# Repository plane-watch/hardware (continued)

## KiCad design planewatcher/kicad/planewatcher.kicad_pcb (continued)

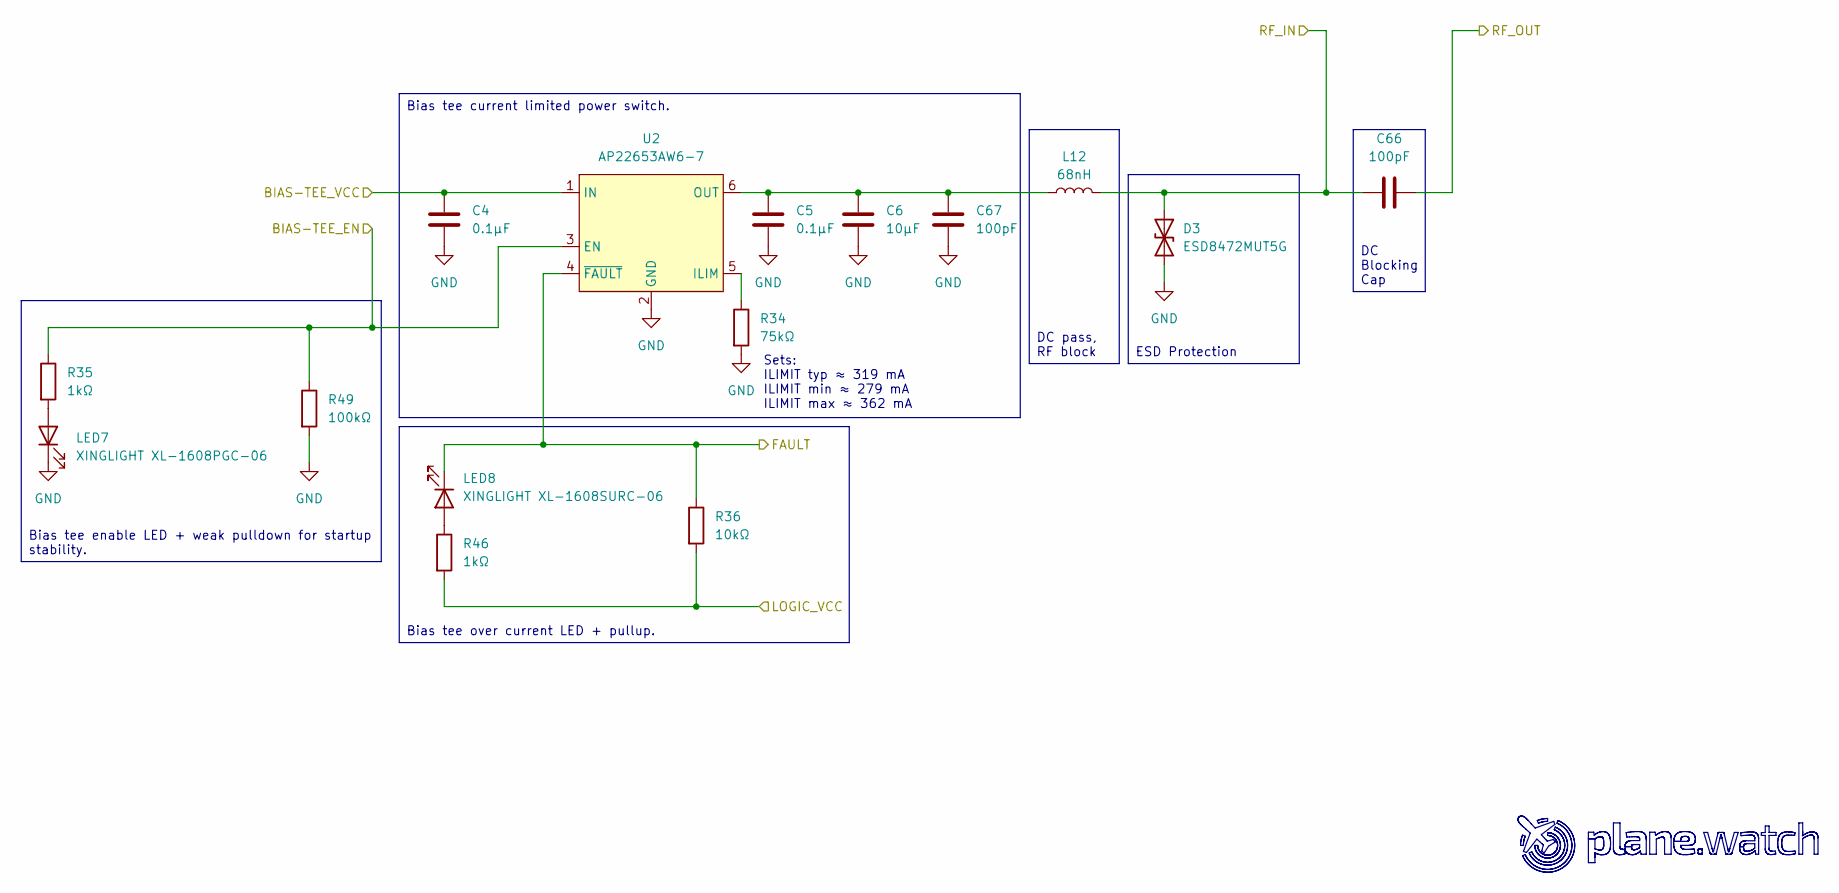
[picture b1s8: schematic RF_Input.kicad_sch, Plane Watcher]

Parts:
C4, C5: 0.1µF; C_0402_1005Metric; MPN GCM155R71A104KA55D; LCSC C161163
C6: 10µF; C_0603_1608Metric; MPN GRM188Z71A106MA73D; LCSC C237435
C66, C67: 100pF; C_0402_1005Metric; MPN GCM1555C1H101FA16D; LCSC C2941926
D3: ESD8472MUT5G; ESD8472; MPN ESD8472MUT5G; LCSC C133346
L12: 68nH; L_Coilcraft_0402DC_1005Metric; MPN 0402DC-68NXJRW; LCSC C3221883
LED7: XINGLIGHT XL-1608PGC-06; LED_0603_1608Metric; MPN XL-1608PGC-06; LCSC C7371905
LED8: XINGLIGHT XL-1608SURC-06; LED_0603_1608Metric; MPN XL-1608SURC-06; LCSC C965799
R34: 75kΩ; R_0402_1005Metric; MPN CRCW040275K0FKED; LCSC C482234
R35, R46: 1kΩ; R_0402_1005Metric; MPN RC0402FR-071KL; LCSC C106235
R36: 10kΩ; R_0402_1005Metric; MPN ERA-2AEB103X; LCSC C191915
R49: 100kΩ; R_0402_1005Metric; MPN CRCW0402100KFKED; LCSC C481918
U2: AP22653AW6-7; SOT26 (Type A1); MPN AP22653AW6-7; LCSC C1511768

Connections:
/FPGA_3V3_BNK35: R36.2, R46.2; also elsewhere on the board
/FPGA_H19: R35.1, R49.1, U2.3 (EN); also elsewhere on the board
/FPGA_H20: LED8.1 (K), R36.1, U2.4 (~FAULT); also elsewhere on the board
/FPGA_VCC_BNK35: C4.2, U2.1 (IN); also elsewhere on the board
/LNA_Stage_1/RF_IN: C66.1; also elsewhere on the board
/RF_Input/RF_IN: C66.2, D3.1 (A1), L12.2; also elsewhere on the board
GND: C4.1, C5.1, C6.1, C67.2, D3.2 (A2), LED7.1 (K), R34.2, R49.2, U2.2 (GND); also elsewhere on the board
unnamed: LED7.2 (A), R35.2
unnamed: LED8.2 (A), R46.1
unnamed: R34.1, U2.5 (ILIM)
unnamed: C5.2, C6.2, C67.1, L12.1, U2.6 (OUT)

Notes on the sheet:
Sets: ILIMIT typ ≈ 319 mA ILIMIT min ≈ 279 mA ILIMIT max ≈ 362 mA
Bias tee enable LED + weak pulldown for startup stability.
Bias tee current limited power switch.
DC Blocking Cap
Bias tee over current LED + pullup.
DC pass, RF block
ESD Protection

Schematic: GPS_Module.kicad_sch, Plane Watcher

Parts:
C59: 10µF; C_0603_1608Metric; MPN GRM188Z71A106MA73D; LCSC C237435
C60, C62: 0.1µF; C_0402_1005Metric; MPN GCM155R71A104KA55D; LCSC C161163
C63: 4.7µF; C_0603_1608Metric; MPN GRM188Z71A475KE15D; LCSC C913474
C74: 10nF; C_0402_1005Metric; MPN CL05B103KB5NNNC; LCSC C15195
D4, D5: ESD8472MUT5G; ESD8472; MPN ESD8472MUT5G; LCSC C133346
J1: 1PPS_OUT; U.FL_Hirose_U.FL-R-SMT-1_Vertical; MPN U.FL-R-SMT-1; LCSC C88374
L10: 600Ω @ 100MHz; L_0805_2012Metric; MPN BLM21SP601SN1D; LCSC C3716677
LED6: XINGLIGHT XL-1608UPC-06; LED_0603_1608Metric; MPN XL-1608UPC-06; LCSC C2977076
R20: 10Ω; R_0402_1005Metric; MPN RE0402DRE0710RL; LCSC C4240446
R21, R23, R24: 33Ω; R_0402_1005Metric; MPN RC0402FR-0733RL; LCSC C138002
R32: 2.2kΩ; R_0402_1005Metric; MPN CRCW04022K20JNED; LCSC C4202009
R33: 49.9Ω 0.5W; R_0805_2012Metric; MPN ERJP06F49R9V; LCSC C77379
R47: 100kΩ; R_0402_1005Metric; MPN CRCW0402100KFKED; LCSC C481918
U1: LEA-M8T; ublox_LEA; MPN LEA-M8T; LCSC C2763452; not fitted
U4: TC4427; MSOP-8_3x3mm_P0.65mm; MPN TC4427EUA713; LCSC C628550

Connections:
4V5: C62.1, C63.1, U4.6 (V_{DD}); also elsewhere on the board
/FPGA_3V3_BNK35: L10.1; also elsewhere on the board
/FPGA_C19: U1.12 (TP2/~SAFEBOOT); also elsewhere on the board
/FPGA_D18: R24.1; also elsewhere on the board
/FPGA_E16: R23.1; also elsewhere on the board
/FPGA_F16: R21.2; also elsewhere on the board
/FPGA_G16: U1.10 (~RESET); also elsewhere on the board
/GPS Module/RF_IN: D4.1 (A1), U1.16 (RF_IN); also elsewhere on the board
GND: C59.2, C60.2, C62.2, C63.2, C74.2, D4.2 (A2), D5.2 (A2), J1.2 (Ext), R32.1, R47.2, U1.7 (GND), U1.13 (GND), U1.14 (GND), U1.15 (GND), U1.17 (GND), U1.24 (VDD_USB), U4.3 (GND); also elsewhere on the board
unnamed: D5.1 (A1), J1.1 (In), R33.2
unnamed: LED6.2 (A), U4.5 (OUT_B)
unnamed: LED6.1 (K), R32.2
unnamed: R24.2, U1.4 (RXD/SPI_MOSI)
unnamed: R21.1, R47.1, U1.28 (TIMEPULSE), U4.2 (IN_A), U4.4 (IN_B)
unnamed: R23.2, U1.3 (TXD/SPI_MISO)
unnamed: C59.1, C60.1, L10.2, U1.6 (VCC), U1.11 (V_BCKP)
unnamed: C74.1, R20.2, U1.18 (VCC_RF)
unnamed: R20.1, U1.19 (V_ANT)
unnamed: R33.1, U4.7 (OUT_A)

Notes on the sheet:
Series damping/termination for FPGA digital I/O
Bypass/decoupling for GPS supply. Ferrite bead ${/7a4a4324-e8b8-4d06-b75a-28095d4e9f10/84812100-48e5-47cc-a358-d48bbae76aaf/2e6ac265-d097-4125-9632-2b6c4976fe0c:REFERENCE} to suppress any high frequency noise back feeding into supply.
If the USB interface is not used, the VDD_USB pin must be connected to GND.
LEA-M8S module includes a built in antenna bias supply for nominal 3 V antennas enabled by linking the filtered VCC_RF supply output pin to the V_ANT antenna supply input pin with a 10 Ohm resistor in series. The module then controls the power supply to the antenna, applying power whenever the rece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
Small series resistor ${/7a4a4324-e8b8-4d06-b75a-28095d4e9f10/84812100-48e5-47cc-a358-d48bbae76aaf/54395c4f-8dde-4acf-ac1a-c77d9f0de467:REFERENCE} feeding FPGA PPS input. Provides edge damping and modest input protection for the FPGA GPIO path. Weak pulldown via ${/7a4a4324-e8b8-4d06-b75a-28095d4e9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
ESD/Transient suppression
Buffers the GPS TIMEPULSE signal and provides enough output current to drive the external 1PPS coax output. Channel A drives the coax connector. Channel B drives the PPS LED.

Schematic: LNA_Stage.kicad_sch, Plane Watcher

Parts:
C28: 1µF; C_0402_1005Metric; MPN GRM155Z71A105KE01D; LCSC C528974
C29: 0.1µF; C_0402_1005Metric; MPN GCM155R71A104KA55D; LCSC C161163
C30: 1nF; C_0402_1005Metric; MPN GCM1555C1H102FA16D; LCSC C126493
C31, C32, C33: 100pF; C_0402_1005Metric; MPN GCM1555C1H101FA16D; LCSC C2941926
L7: 68nH; L_0603_1608Metric; MPN 0603CS-68NXJLW; LCSC C19191685
U7: TQP3M9036; U_Qorvo_TQP3M9036-QFN; MPN TQP3M9036; LCSC C920261
Z8, Z12: 0Ω; R_0402_1005Metric; MPN ERJ-2GE0R00X; LCSC C242160
Z13: 68nH; L_0402_1005Metric; MPN 0402DC-68NXJRW; LCSC C3221883
Z15, Z17, Z18: TBD; R_0402_1005Metric; not fitted

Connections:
3V3: C28.2, C29.1, C30.1, C31.2, L7.1; also elsewhere on the board
/LNA_Stage_1/RF_IN: Z8.1, Z13.2; also elsewhere on the board
/LNA_Stage_1/RF_OUT: Z12.2, Z18.2; also elsewhere on the board
GND: C28.1, C29.2, C30.2, C31.1, U7.1 (NC), U7.3 (NC), U7.4 (NC), U7.5 (NC), U7.6 (Shutdown), U7.8 (NC), U7.EP (GND), Z13.1, Z15.1, Z17.1, Z18.1; also elsewhere on the board
unnamed: C32.2, Z8.2, Z15.2
unnamed: C33.1, Z12.1, Z17.2
unnamed: C32.1, U7.2 (RF_In)
unnamed: C33.2, L7.2, U7.7 (RF_Out)

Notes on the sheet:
Pi pad for RF matching. Testing of prototype 1.3 showed population of 68nH at ${/7a4a4324-e8b8-4d06-b75a-28095d4e9f10/be54cab6-561b-439c-9db3-5433a1e68d46/9edbfe7c-c1e3-43ce-82d9-521a4853e503:REFERENCE} improves RF performance significantly. DNP pads & 0ΩR allow for future population of L/C/R compo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
DC block, RF pass
Pi pad for RF matching DNP pads & 0ΩR allow for future population of L/C/R components to improve impedance (Z) matching.
Shutdown tied to GND for always-on.
RF block, DC pass
Supply decoupling & bypassing.
RF_IN and RF_OUT are 50Ω controlled-impedance RF traces. Keep short. No stubs. Reference solid GND plane.

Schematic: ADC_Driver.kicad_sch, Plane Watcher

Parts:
C7, C8: CF_DNP; C_0402_1005Metric; not fitted
C9: 2.2µF; C_0805_2012Metric; MPN CL21B225KBYVPNE; LCSC C5362585
C46, C48, C65, C82: 0.1µF; C_0402_1005Metric; MPN GCM155R71A104KA55D; LCSC C161163
C47, C64, C80, C81: 10µF; C_0603_1608Metric; MPN GRM188Z71A106MA73D; LCSC C237435
C71, C72: 20pF; C_0402_1005Metric; MPN GJM1555C1H200FB01D; LCSC C913479; not fitted
C78: 100pF; C_0402_1005Metric; MPN GCM1555C1H101FA16D; LCSC C2941926
C79: 1nF; C_0402_1005Metric; MPN GCM1555C1H102FA16D; LCSC C126493
R3: R_BASE_GND_DNP; R_0402_1005Metric; MPN ERJ-2GE0R00X; LCSC C242160; not fitted
R28, R29: 10kΩ; R_0402_1005Metric; MPN ERA-2AEB103X; LCSC C191915
R30, R31: 49.9Ω; R_0402_1005Metric; MPN RT0402BRD0749R9L; LCSC C852809
R51: 1MΩ; R_0402_1005Metric; MPN ERJ2RKF1004X; LCSC C413126
RN1: 4x 499Ω 1%; R_Array_Convex_4x0402; MPN 4D02WGF4990TCE; LCSC C620896
TP2: Noise Floor; TestPoint_THTPad_D1.0mm_Drill0.5mm; not fitted
TP15: VOCM; TestPoint_THTPad_D1.0mm_Drill0.5mm; not fitted
U3: OPA320; SOT-23-5; MPN OPA320AIDBVR; LCSC C92494
U10: AD8138; SOIC-8_3.9x4.9mm_P1.27mm; MPN AD8138ARZ; LCSC C113762
U12: ADA4807-1; SOT-23-6; MPN ADA4807-1ARJZ; LCSC C2058411

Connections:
3V3: C47.1, C48.1, C64.1, C65.1, C81.1, C82.1, R28.1, U3.5 (V+), U10.3 (V+), U12.5 (~DISABLE), U12.6 (+V_{S}); also elsewhere on the board
/ADC/AINN: C72.1, R30.2; also elsewhere on the board
/ADC/AINP: C71.2, R31.2; also elsewhere on the board
/ADC_Driver/VLOG_IN: U12.3 (+IN); also elsewhere on the board
GND: C9.2, C46.2, C47.2, C48.2, C64.2, C65.2, C71.1, C72.2, C78.2, C79.1, C80.2, C81.2, C82.2, R3.2, R29.2, U3.2 (V-), U10.6 (V-), U12.2 (-V_{S}); also elsewhere on the board
unnamed: C7.1, RN1.1 (R1.1), RN1.7 (R2.2), U10.1 (-IN)
unnamed: RN1.8 (R1.2), U3.1 (OUT), U3.4 (-IN)
unnamed: C7.2, R30.1, RN1.2 (R2.1), U10.4 (+OUT)
unnamed: C8.2, R31.1, RN1.3 (R3.1), U10.5 (-OUT)
unnamed: C8.1, RN1.4 (R4.1), RN1.6 (R3.2), U10.8 (+IN)
unnamed: R51.2, RN1.5 (R4.2), U12.1 (VOUT), U12.4 (-IN)
unnamed: C9.1, R3.1, R51.1, TP2.1 (1_1), U3.3 (+IN)
unnamed: C46.1, C78.1, C79.2, C80.1, R28.2, R29.1, TP15.1 (1_1), U10.2 (VOCM)

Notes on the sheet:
Unity-gain buffer for low-pass filter output
AD8138 Gain/Feedback
Supply decoupling
Slow analog baseline / noise-floor LPF ${/7a4a4324-e8b8-4d06-b75a-28095d4e9f10/cbd39e42-d959-46e0-ad78-463479feebd1/ae7df914-0de9-4d72-bf9b-651d07cfcad7:REFERENCE} and ${/7a4a4324-e8b8-4d06-b75a-28095d4e9f10/cbd39e42-d959-46e0-ad78-463479feebd1/846c36a3-17d8-4d50-ba34-5eeb3035e41e:REFERENCE} form a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
Unity-gain buffer for log detector output
Set common-mode voltage to 3V3/2 = 1.65V
Series output isolation/termination resistors between AD8138 output and AD9203 input. Shunt cap footprints added to tune ADC input filtering/settling if required.
VOCM decoupling/bypassing

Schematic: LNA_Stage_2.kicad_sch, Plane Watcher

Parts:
C34: 1µF; C_0402_1005Metric; MPN GRM155Z71A105KE01D; LCSC C528974
C35: 0.1µF; C_0402_1005Metric; MPN GCM155R71A104KA55D; LCSC C161163
C36: 1nF; C_0402_1005Metric; MPN GCM1555C1H102FA16D; LCSC C126493
C37, C38, C39: 100pF; C_0402_1005Metric; MPN GCM1555C1H101FA16D; LCSC C2941926
L8: 68nH; L_0603_1608Metric; MPN 0603CS-68NXJLW; LCSC C19191685
R9: 0Ω; R_0402_1005Metric; MPN ERJ-2GE0R00X; LCSC C242160
U8: TQP3M9036; U_Qorvo_TQP3M9036-QFN; MPN TQP3M9036; LCSC C920261
Z14: TBD; L_0402_1005Metric; not fitted
Z16, Z19, Z21: TBD; R_0402_1005Metric; not fitted
Z20: 0Ω; R_0402_1005Metric; MPN ERJ-2GE0R00X; LCSC C242160

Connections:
3V3: C34.2, C35.1, C36.1, C37.2, L8.1; also elsewhere on the board
/LNA_Stage_2/RF_IN: R9.1, Z14.2; also elsewhere on the board
/LNA_Stage_2/RF_OUT: Z20.2, Z21.2; also elsewhere on the board
GND: C34.1, C35.2, C36.2, C37.1, U8.1 (NC), U8.3 (NC), U8.4 (NC), U8.5 (NC), U8.6 (Shutdown), U8.8 (NC), U8.EP (GND), Z14.1, Z16.1, Z19.1, Z21.1; also elsewhere on the board
unnamed: C38.2, R9.2, Z16.2
unnamed: C39.1, Z19.2, Z20.1
unnamed: C38.1, U8.2 (RF_In)
unnamed: C39.2, L8.2, U8.7 (RF_Out)

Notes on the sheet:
Pi pad for RF matching DNP pads & 0ΩR allow for future population of L/C/R components to improve impedance (Z) matching.
RF block, DC pass
DC block, RF pass
Shutdown tied to GND for always-on.
RF_IN and RF_OUT are 50Ω controlled-impedance RF traces. Keep short. No stubs. Reference solid GND plane.
Supply decoupling & bypassing.

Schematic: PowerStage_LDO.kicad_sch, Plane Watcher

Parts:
C2, C22: 0.1µF; C_0402_1005Metric; MPN GCM155R71A104KA55D; LCSC C161163
C3: 1nF; C_0402_1005Metric; MPN GCM1555C1H102FA16D; LCSC C126493
C19: 4.7µF; C_1206_3216Metric; MPN CL31B475KBHNNNE; LCSC C51205; not fitted
C21: 4.7µF; C_1206_3216Metric; MPN CL31B475KBHNNNE; LCSC C51205
C26: 4.7µF; C_0603_1608Metric; MPN GRM188Z71A475KE15D; LCSC C913474
C27: 22µF; C_1206_3216Metric; MPN CL31B226KPHNNNE; LCSC C87996
L5: 600Ω @ 100MHz; L_0805_2012Metric; MPN BLM21SP601SN1D; LCSC C3716677
R18: 10kΩ; R_0402_1005Metric; MPN ERA-2AEB103X; LCSC C191915
R19: 93.1kΩ; R_0402_1005Metric; MPN TNPW040293K1BEED; LCSC C2088785
R22: 33.2kΩ; R_0603_1608Metric; MPN RT0603BRB0733K2L; LCSC C860335
TP1: 3V3; TestPoint_THTPad_D1.0mm_Drill0.5mm; not fitted
U6: LT3045/LT3045-1; U_LT3045IMSE-1_PBF; MPN LT3045IMSE#TRPBF; LCSC C666587

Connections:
3V3: C2.1, C3.1, C27.1, R19.2, TP1.1 (1_1), U6.10 (OUTS), U6.11 (OUT), U6.12 (OUT); also elsewhere on the board
4V5: C19.1, L5.1; also elsewhere on the board
/PWR_GOOD: U6.5 (PG); also elsewhere on the board
GND: C2.2, C3.2, C19.2, C21.2, C22.2, C26.1, C27.2, R18.1, R22.1, U6.6 (ILIM), U6.9 (GND), U6.13 (GND); also elsewhere on the board
unnamed: C21.1, C22.1, L5.2, U6.1 (IN), U6.2 (IN), U6.4 (EN/UV)
unnamed: R18.2, R19.1, U6.7 (PGFB)
unnamed: C26.2, R22.2, U6.8 (SET)

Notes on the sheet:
${/7a4a4324-e8b8-4d06-b75a-28095d4e9f10/e02d84ed-6468-4290-a59c-50ded41c0aba/d0620f5f-b1cf-4df8-a6ae-ece97448600e:REFERENCE} marked DNP to adhere to USB capacitance limit (although FPGA board waaaaay exceeds the limit anyway...)
Set VOUT to 3.32V
KiCad cannot infer power through inductors/beads/filter parts.
Attempt to suppress digital noise coming in from power supply.
PG asserts nominally at 3.09 V, guaranteed by 3.20 V.
OUTS kelvin connected to output bulk cap
HF transient suppression
Input bulk.

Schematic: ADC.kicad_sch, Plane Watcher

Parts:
C49, C52, C55, C58: 10µF; C_0603_1608Metric; MPN GRM188Z71A106MA73D; LCSC C237435
C50, C51, C53, C54, C56, C57: 0.1µF; C_0402_1005Metric; MPN GCM155R71A104KA55D; LCSC C161163
C68, C73, C77: 1nF; C_0402_1005Metric; MPN GCM1555C1H102FA16D; LCSC C126493
C69, C75, C76: 100pF; C_0402_1005Metric; MPN GCM1555C1H101FA16D; LCSC C2941926
L6, L9: 600Ω @ 100MHz; L_0805_2012Metric; MPN BLM21SP601SN1D; LCSC C3716677
R4: 0Ω; R_0402_1005Metric; MPN ERJ-2GE0R00X; LCSC C242160; not fitted
R5: 0Ω; R_0402_1005Metric; MPN ERJ-2GE0R00X; LCSC C242160
RN2, RN3, RN4: 4x 22Ω 1%; R_Cat16-4; MPN CAY16-22R0F4LF; LCSC C1734385
U11: AD9203ARUZ; TSSOP-28_4.4x9.7mm_P0.65mm; MPN AD9203ARUZ; LCSC C653239

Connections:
3V3: L9.2; also elsewhere on the board
/ADC/ADC_AVDD: C51.1, C52.1, C73.2, C75.1, L9.1, U11.21 (PWRCON), U11.28 (AVDD)
/ADC/ADC_DRVDD: C49.1, C50.1, C68.2, C69.1, L6.2, U11.2 (DRVDD)
/ADC/AINN: U11.26 (AINN); also elsewhere on the board
/ADC/AINP: U11.25 (AINP); also elsewhere on the board
/FPGA_3V3_BNK33: L6.1; also elsewhere on the board
/FPGA_AA19: RN3.2 (R2.1); also elsewhere on the board
/FPGA_AB14: RN2.3 (R3.1); also elsewhere on the board
/FPGA_AB16: RN3.1 (R1.1); also elsewhere on the board
/FPGA_AB19: RN3.3 (R3.1); also elsewhere on the board
/FPGA_AB21: RN3.4 (R4.1); also elsewhere on the board
/FPGA_AB22: RN4.3 (R3.1); also elsewhere on the board
/FPGA_U22: RN4.4 (R4.1); also elsewhere on the board
/FPGA_V13: RN2.1 (R1.1); also elsewhere on the board
/FPGA_W22: RN4.1 (R1.1); also elsewhere on the board
/FPGA_Y13: RN2.2 (R2.1); also elsewhere on the board
/FPGA_Y18: RN2.4 (R4.1); also elsewhere on the board
/FPGA_Y21: RN4.2 (R2.1); also elsewhere on the board
GND: C49.2, C50.2, C51.2, C52.2, C53.2, C56.2, C57.2, C58.2, C68.1, C69.2, C73.1, C75.2, C76.2, C77.1, R5.2, U11.1 (DRVSS), U11.14 (DFS), U11.16 (3-STATE), U11.17 (STBY), U11.19 (CLAMP), U11.20 (CLAMPIN), U11.27 (AVSS); also elsewhere on the board
unnamed: RN2.8 (R1.2), U11.3 (D0)
unnamed: RN2.7 (R2.2), U11.4 (D1)
unnamed: RN2.6 (R3.2), U11.5 (D2)
unnamed: RN2.5 (R4.2), U11.6 (D3)
unnamed: RN3.8 (R1.2), U11.7 (D4)
unnamed: RN3.7 (R2.2), U11.8 (D5)
unnamed: RN3.6 (R3.2), U11.9 (D6)
unnamed: RN3.5 (R4.2), U11.10 (D7)
unnamed: RN4.8 (R1.2), U11.13 (OTR)
unnamed: RN4.7 (R2.2), U11.12 (D9)
unnamed: RN4.6 (R3.2), U11.11 (D8)
unnamed: RN4.5 (R4.2), U11.15 (CLK)
unnamed: C53.1, C54.1, C55.1, U11.24 (REFBF)
unnamed: R4.1, R5.1, U11.18 (REFSENSE)
unnamed: C54.2, C55.2, C56.1, U11.22 (REFTF)
unnamed: C57.1, C58.1, C76.1, C77.2, R4.2, U11.23 (VREF)

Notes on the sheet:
Series damping/termination for FPGA digital I/O
Bypass/decoupling for digital supply. Ferrite bead ${/7a4a4324-e8b8-4d06-b75a-28095d4e9f10/f77ae351-26f3-42d4-beb0-b884b17c3798/533e3aea-0b01-471e-8965-b1a7ec8870ac:REFERENCE} to suppress any high frequency noise entering digital supply.
Bypass/decoupling for analog supply. Ferrite bead ${/7a4a4324-e8b8-4d06-b75a-28095d4e9f10/f77ae351-26f3-42d4-beb0-b884b17c3798/90bf33f2-24fe-4a1e-9477-6f6210e09237:REFERENCE} to suppress any high frequency noise entering quiet analog supply.
VREF decoupling
Top and Bottom Reference Decoupling (as-per datasheet)
Ability to change 1Vp-p to 2Vp-p. 2Vp-p as-per schematic with ${/7a4a4324-e8b8-4d06-b75a-28095d4e9f10/f77ae351-26f3-42d4-beb0-b884b17c3798/c2c460cc-af40-46f2-a17d-a1fcea9bb573:REFERENCE} DNP and ${/7a4a4324-e8b8-4d06-b75a-28095d4e9f10/f77ae351-26f3-42d4-beb0-b884b17c3798/ce9a091b-3b33-4179-8729-958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

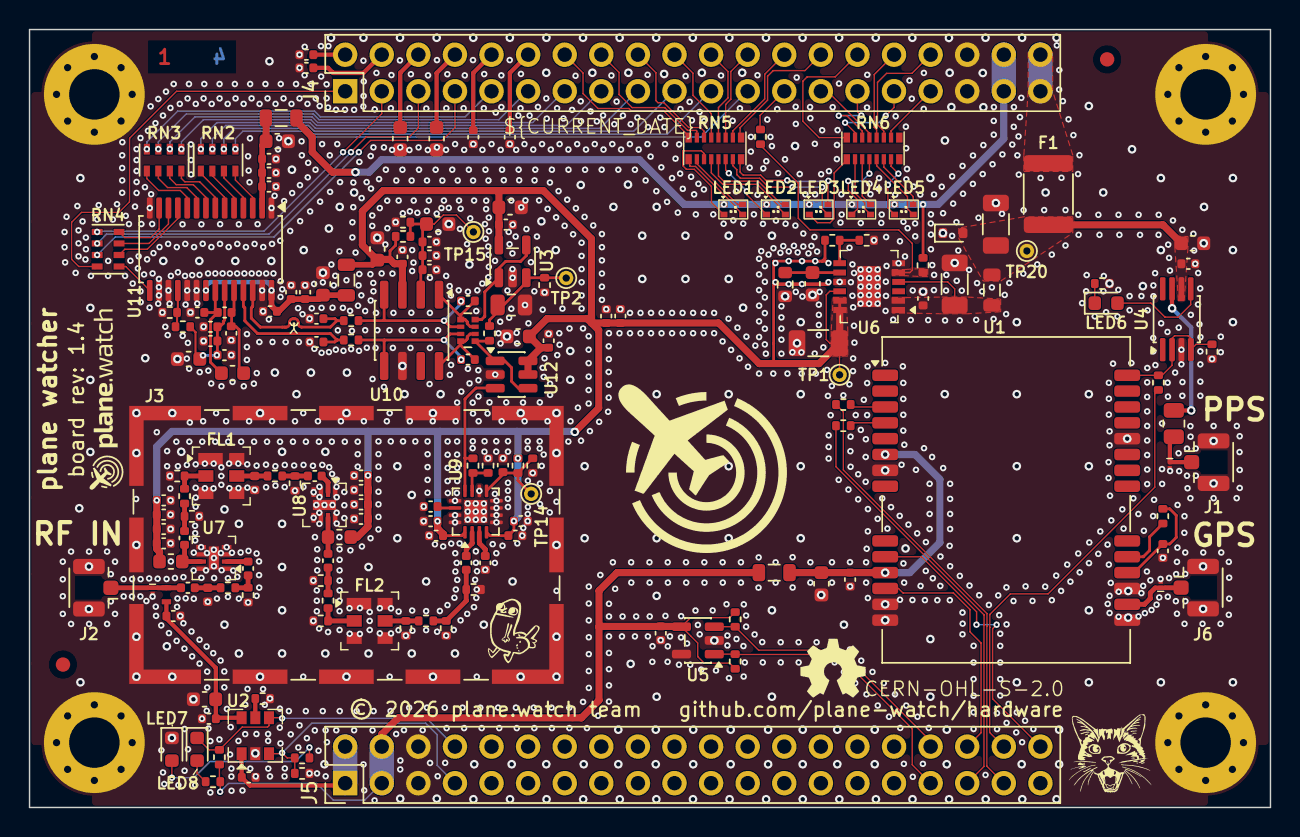
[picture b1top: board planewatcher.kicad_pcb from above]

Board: 4 copper layers, 86.1 x 54.0 mm, 179 parts (0 on the bottom side), 133 nets.

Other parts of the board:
FID2, FID3: Fiducial_1mm_Mask2mm
MH1, MH2, MH3, MH4: MountingHole_3.5mm_Pad_Via

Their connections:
GND: MH1.1, MH2.1, MH3.1, MH4.1; also elsewhere on the board

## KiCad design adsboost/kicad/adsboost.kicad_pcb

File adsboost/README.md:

# ADSBoost

**ADSBoost** is an open source, receive-only LNA and SAW filter module for 1090 MHz ADS-B and Mode S reception. It is intended to be installed close to the antenna and powered through its RF output coax using a bias tee.

<div style="text-align: center;"></div>

## Expected performance

> ADSBoost is currently a prototype. The module-level figures below are design estimates derived from the component datasheets; they are not production-tested. They will be replaced with measured results after the first assembled boards have been characterised.

| Parameter | Expected performance | Notes |
| --- | --- | --- |
| Application | 1090 MHz ADS-B and Mode S reception | Receive only; do not connect the input to a transmitter |
| Centre frequency | 1090 MHz | Set by the TA2003A SAW filter |
| Specified passband | 1087-1093 MHz | 6 MHz nominal filter bandwidth |
| In-band gain | Approximately 15 dB typical | Estimated from approximately 18 dB LNA gain at 1090 MHz minus 3.2 dB typical SAW insertion loss and small PCB losses |
| Noise figure | Approximately 0.5-0.7 dB expected | Estimate including the input network; measurement pending |
| RF impedance | 50 ohms nominal | Both ports |
| Operating temperature | -40 to +85 degrees C design range | Limited by the SAW filter; module not yet environmentally qualified |
| Supply voltage | See [Powering ADSBoost](#powering-adsboost) | DC is supplied through the RF output connector |
| Supply current | Approximately 45-68 mA typical | Depends on supply voltage; allow at least 100 mA from the bias tee |

The [Qorvo TQP3M9036](<datasheets/TQP3M9036 Data Sheet.pdf>) LNA has approximately 18.4 dB typical gain and 0.42 dB minimum noise figure around 1090 MHz when operated from 5 V. The [TA2003A datasheet](<datasheets/TA2003A _Rev.1.0_.pdf>) specifies 3.2 dB typical and 4.0 dB maximum insertion loss across 1087-1093 MHz.

The SAW filter also specifies the following out-of-band attenuation. These are component specifications rather than measured module limits.

| Frequency range | Minimum attenuation |
| --- | ---: |
| DC-970 MHz | 45 dB |
| 1046 MHz | 40 dB |
| 1150-1300 MHz | 45 dB |

Module input/output return loss, gain variation, compression point and linearity remain to be measured on assembled hardware.

## RF matching and tuning

Three 0402 pi-pad matching networks are provided along the RF path: one at the LNA input, one between the LNA and SAW filter, and one after the SAW filter. They are fitted as straight-through links by default, with a 0 ohm series resistor and both shunt positions left unpopulated.

After assembled boards have been measured with a VNA, the footprints can be populated with suitable resistor, capacitor or inductor values to refine the 1090 MHz matching and compensate for real-world PCB and component parasitics.

## Connections

| Connector | Function |
| --- | --- |
| `J1` / `ANT_IN` | RF input from the antenna; no DC should be applied here |
| `J2` / `RF_OUT+BIAS` | Amplified and filtered RF output, and positive DC bias input |

## Powering ADSBoost

ADSBoost is powered through `J2` using a bias tee. The coax centre conductor must be positive and the shield must be ground. The bias tee should present the DC supply on its RF+DC port while preventing that DC from reaching the receiver's RF input.

The [TQP3M9036 datasheet](<datasheets/TQP3M9036 Data Sheet.pdf>) specifies:

| LNA operating point | Device supply current |
| --- | ---: |
| 3.3 V | Approximately 45 mA typical |
| 4.0 V | Approximately 50 mA typical |
| 5.0 V | Approximately 68 mA typical; 40-90 mA datasheet range |

The LNA's recommended device supply range is **3.3-5.25 V**. ADSBoost includes a 1 ohm series protection/filter resistor, which introduces a small voltage drop. Therefore:

- Supply **3.4-5.0 V DC at `J2`**, with 5.0 V recommended.
- Use a low-noise, regulated supply capable of at least **100 mA**.
- Treat all stated voltages as voltages at the module. Coax and bias-tee resistance may produce an additional voltage drop.
- Do not apply DC to `J1`.
- Do not reverse the supply polarity.

### Overvoltage warning

The board includes a [BZT52C6V2](https://www.diodes.com/part/view/BZT52C6V2/) 6.2 V zener diode and a 1 ohm series resistor to help clamp short transients. **This circuit is not a voltage regulator and does not make sustained overvoltage safe.**

Do not exceed the LNA's 5.25 V recommended operating limit. Its 7 V absolute maximum rating is a damage threshold, not an acceptable supply voltage. A sustained excessive voltage can overheat or destroy the zener diode, series resistor and LNA. In particular, applying 12 V through a common masthead-amplifier bias supply is likely to damage the module.

## Enclosure

ADSBoost is designed to fit either of these 100 mm split aluminium enclosures from JLCMC:

- [Aluminum Box (JLC) – 25 × 25 × 40 mm, Split (K1-2525-H6-L40), Natural](<https://jlcmc.com/product/b/U01/BR12070/aluminum-box-(jlc)-25*25*100mm-split>)
- [Aluminum Box (JLC) – 25 × 25 × 40 mm, Split (K1-2525-H7-L40), Black](<https://jlcmc.com/product/b/U01/BR12071/aluminum-box-(jlc)-125*25*100-split>)

Installation requires one **6.6 mm diameter hole in the centre of each end cap**, aligned with the RF connectors.

## License

The hardware design files are licensed under the [CERN Open Hardware Licence Version 2 – Strongly Reciprocal (CERN-OHL-S-2.0)](LICENSE).

The CERN-OHL-S-2.0 permits commercial use, but its reciprocal requirements apply when covered source or products based on it are distributed.

Alternative commercial licensing is available for companies that need different terms.

TL;DR: You can use and modify the design privately. If you distribute modified source or products based on it, the CERN-OHL-S-2.0 requirements apply. If those terms do not work for you, talk to us.

## Notice

This repository may include third-party datasheets, application notes, and technical documentation.

Such materials remain the copyright of their respective owners and are included solely to assist development and interoperability of this project.

If you are a copyright holder and have concerns regarding included materials, please open an issue or contact the maintainers.

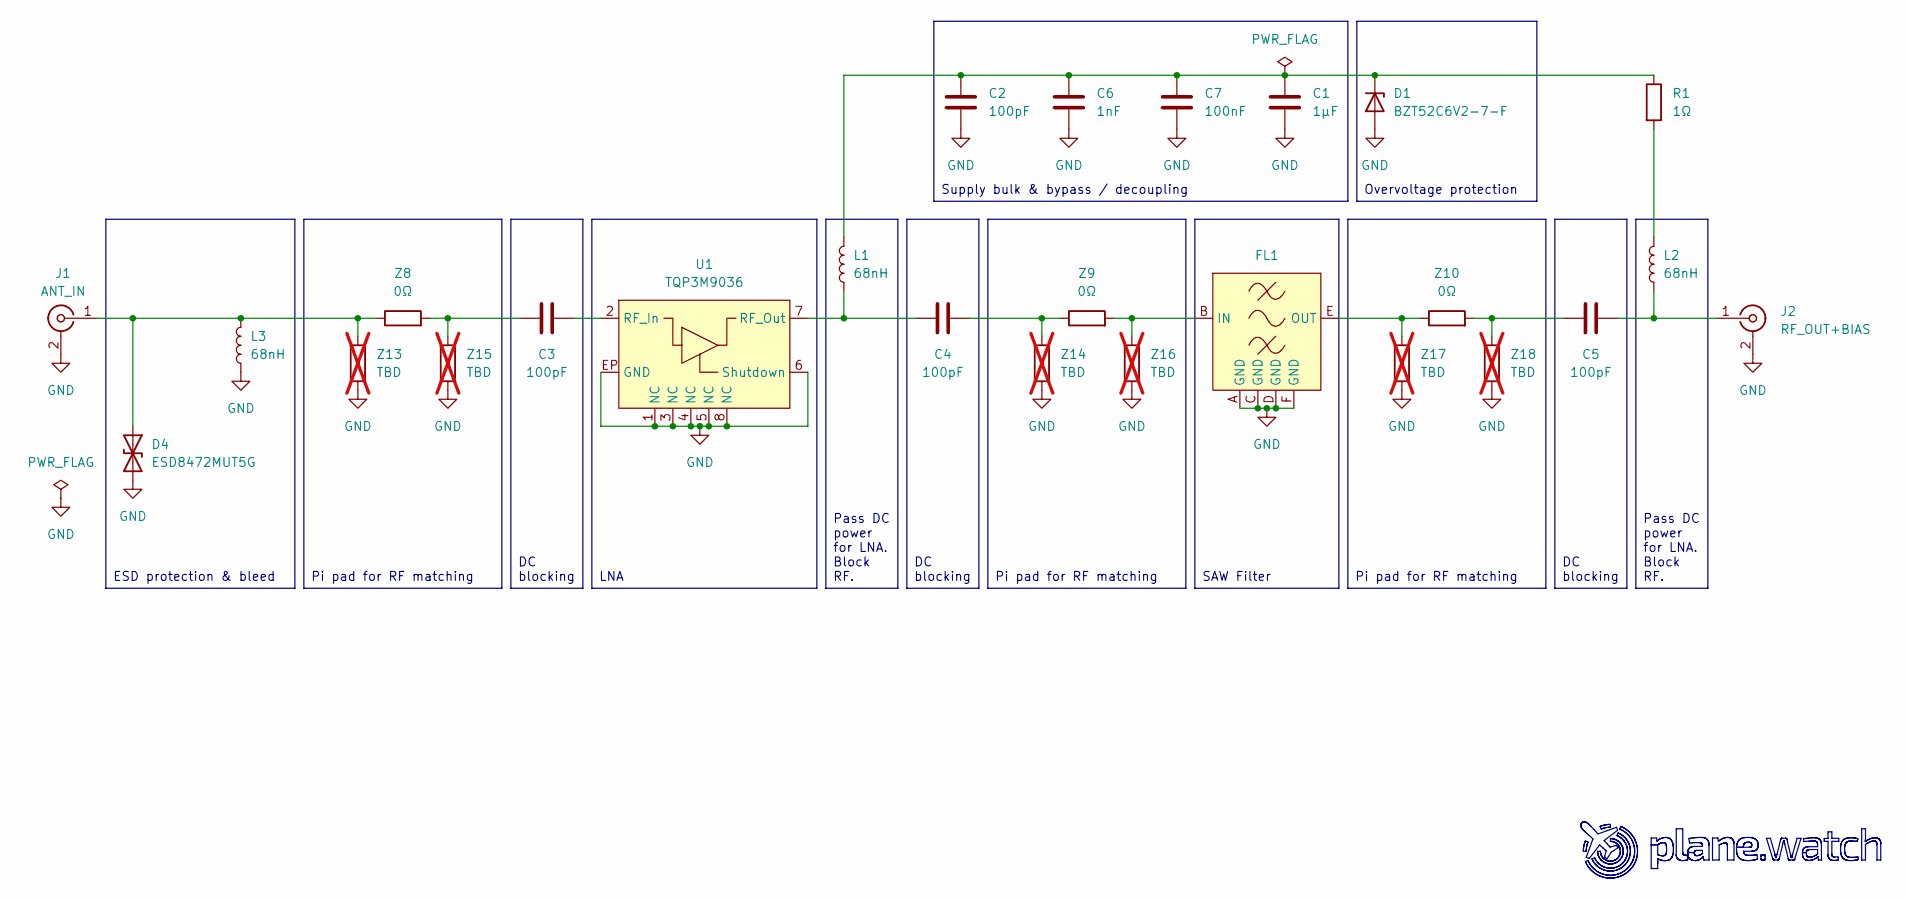
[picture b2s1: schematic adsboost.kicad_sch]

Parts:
C1: 1µF; C_0603_1608Metric; lcsc_id C85862
C2, C3, C4, C5: 100pF; C_0402_1005Metric; lcsc_id C2941926
C6: 1nF; C_0402_1005Metric; lcsc_id C126493
C7: 100nF; C_0402_1005Metric; lcsc_id C161163
D1: BZT52C6V2-7-F; D_SOD-123; lcsc_id C397931
D4: ESD8472MUT5G; ESD8472; MPN ESD8472MUT5G; lcsc_id C133346
FL1: TA2003A; FL_Tai-Saw_TA2003A
J1: ANT_IN; Amphenol 132289; lcsc_id C3172723
J2: RF_OUT+BIAS; Amphenol 132289; lcsc_id C3172723
L1, L2, L3: 68nH; L_Coilcraft_0402DC_1005Metric; MPN 0402DC-68NXJRW; lcsc_id C3221883
R1: 1Ω; R_0805_2012Metric; lcsc_id C313850
U1: TQP3M9036; U_Qorvo_TQP3M9036-QFN; lcsc_id C920261
Z8, Z9, Z10: 0Ω; R_0402_1005Metric; MPN ERJ-2GE0R00X; lcsc_id C242160
Z13, Z14, Z15, Z16, Z17, Z18: TBD; R_0402_1005Metric; not fitted

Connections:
GND: C1.2, C2.2, C6.2, C7.2, D1.2 (A), D4.2 (A2), FL1.A (GND), FL1.C (GND), FL1.D (GND), FL1.F (GND), J1.2 (Ext), J2.2 (Ext), L3.1, U1.1 (NC), U1.3 (NC), U1.4 (NC), U1.5 (NC), U1.6 (Shutdown), U1.8 (NC), U1.EP (GND), Z13.1, Z14.1, Z15.1, Z16.1, Z17.1, Z18.1
unnamed: C3.2, Z8.2, Z15.2
unnamed: C4.1, Z9.1, Z14.2
unnamed: C5.2, Z10.2, Z18.2
unnamed: C1.1, C2.1, C6.1, C7.1, D1.1 (K), L1.2, R1.1
unnamed: D4.1 (A1), J1.1 (In), L3.2, Z8.1, Z13.2
unnamed: FL1.B (IN), Z9.2, Z16.2
unnamed: FL1.E (OUT), Z10.1, Z17.2
unnamed: C5.1, J2.1 (In), L2.1
unnamed: L2.2, R1.2
unnamed: C3.1, U1.2 (RF_In)
unnamed: C4.2, L1.1, U1.7 (RF_Out)

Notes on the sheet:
Pi pad for RF matching
LNA
Overvoltage protection
Supply bulk & bypass / decoupling
DC blocking
ESD protection & bleed
Pass DC power for LNA. Block RF.
SAW Filter

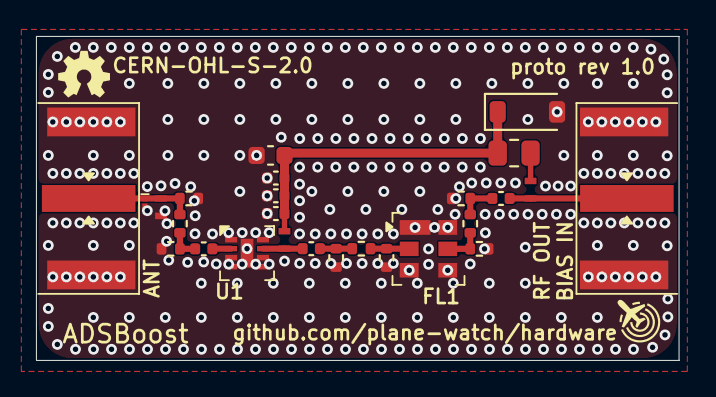
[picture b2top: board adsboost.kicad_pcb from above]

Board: 4 copper layers, 35.7 x 18.0 mm, 26 parts (0 on the bottom side), 12 nets.

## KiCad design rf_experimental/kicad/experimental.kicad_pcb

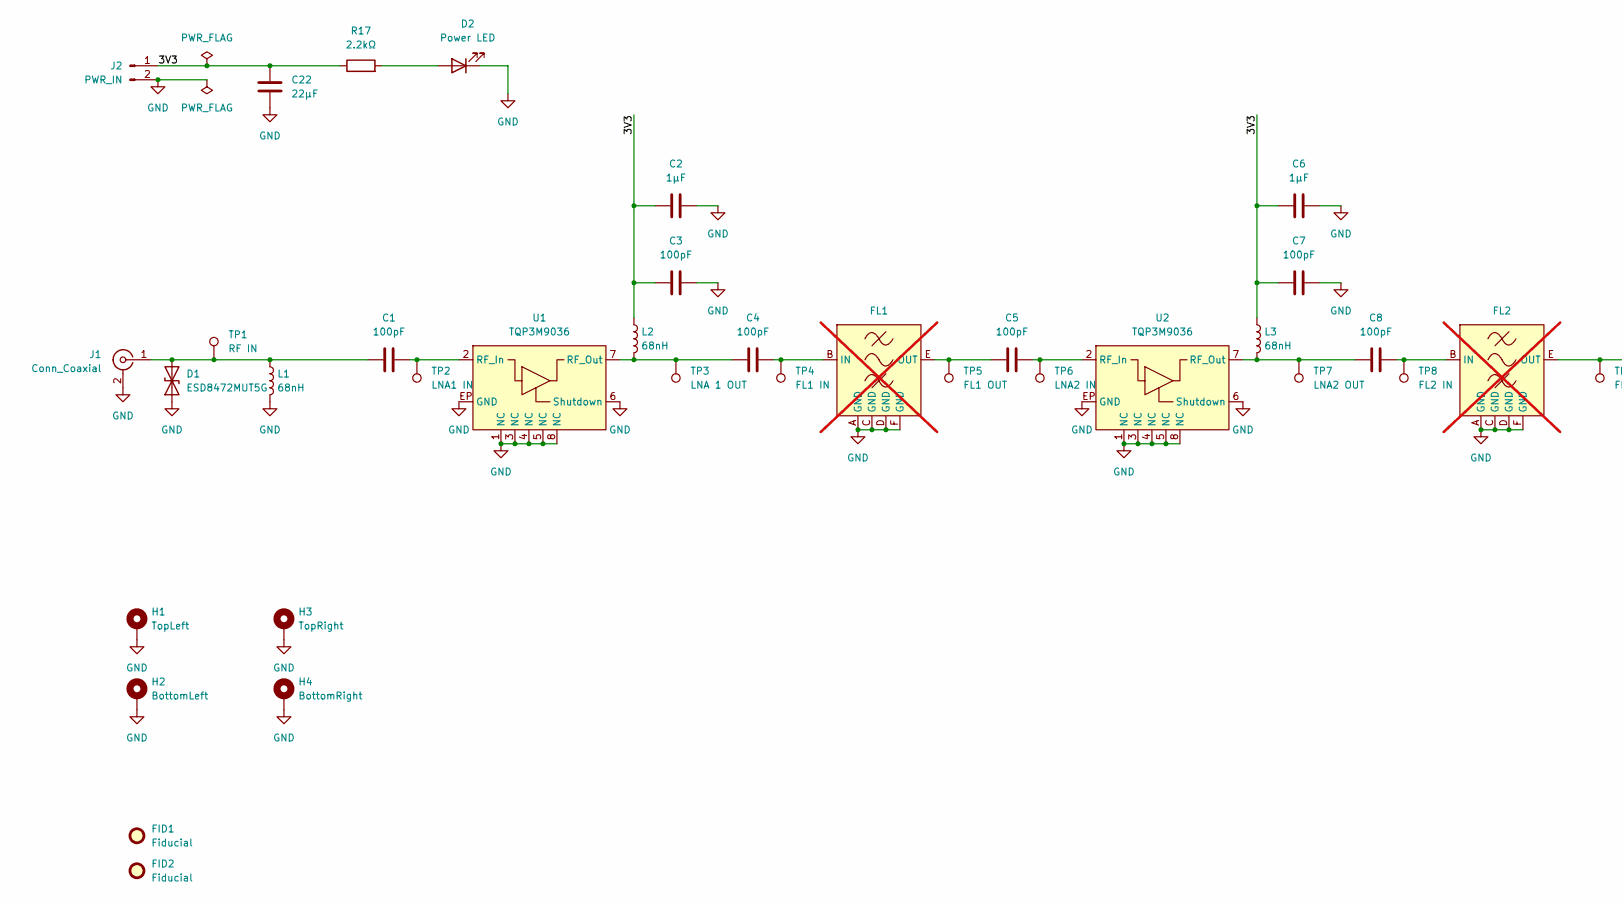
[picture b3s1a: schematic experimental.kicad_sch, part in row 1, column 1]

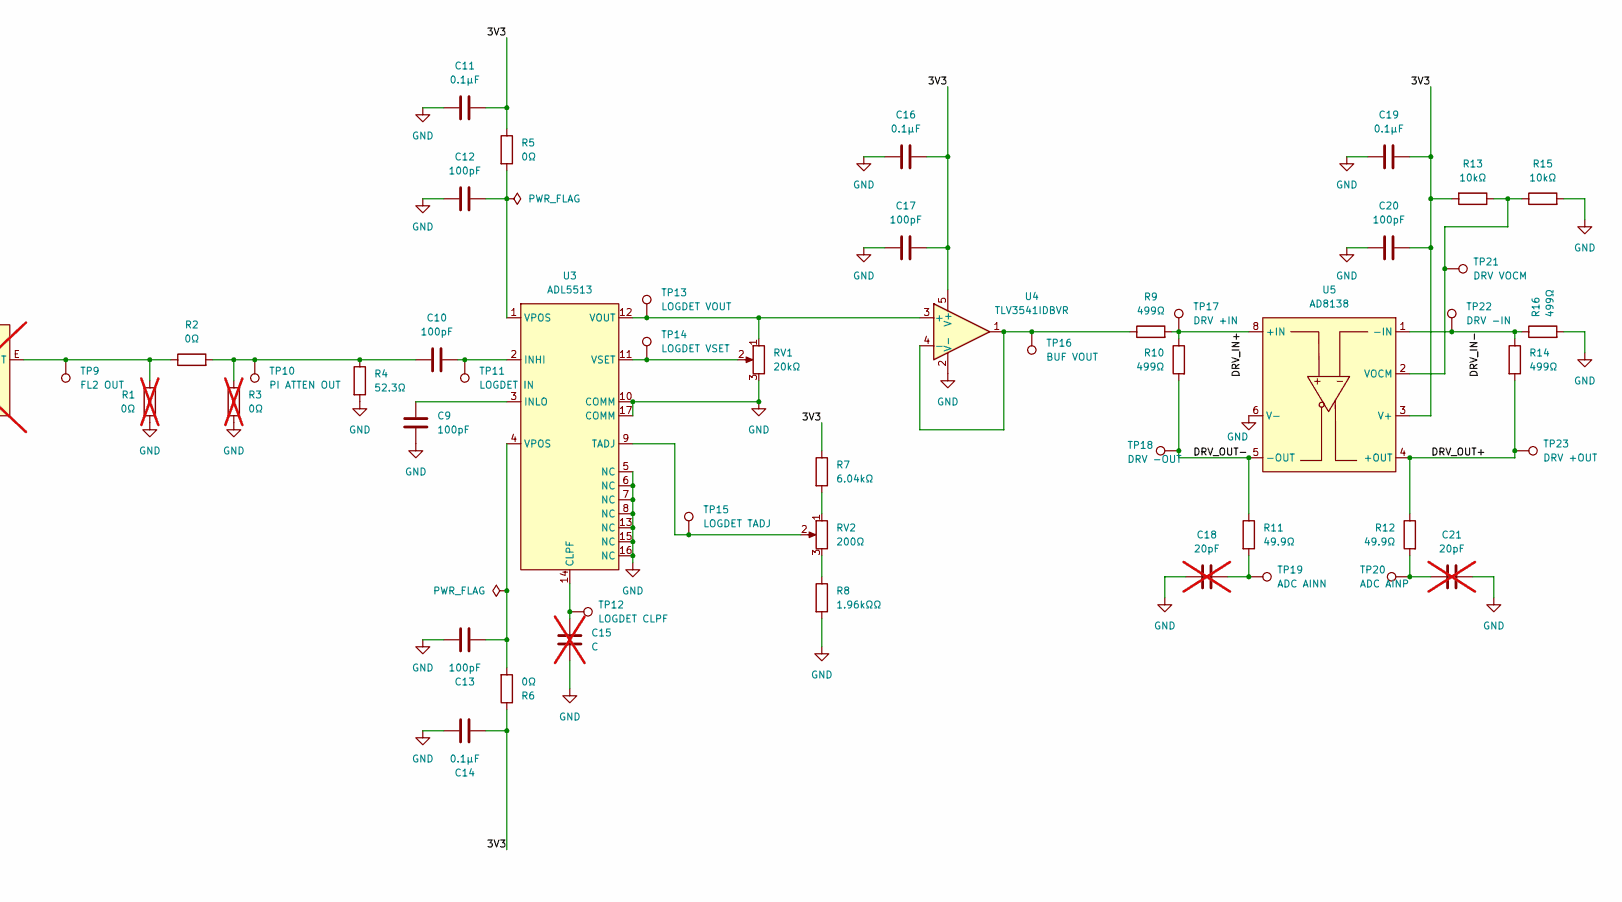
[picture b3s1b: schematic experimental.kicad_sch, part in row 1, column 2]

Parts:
C1, C3, C4, C5, C7, C8, C9, C10, C12, C13, C17, C20: 100pF; C_0402_1005Metric_Pad0.74x0.62mm_HandSolder; LCSC ID # C2941926
C2, C6: 1µF; C_0603_1608Metric_Pad1.08x0.95mm_HandSolder; LCSC ID # C519559
C11, C14, C16, C19: 0.1µF; C_0402_1005Metric_Pad0.74x0.62mm_HandSolder; LCSC ID # C913742
C15: C; C_0402_1005Metric_Pad0.74x0.62mm_HandSolder; not fitted
C18, C21: 20pF; C_0402_1005Metric_Pad0.74x0.62mm_HandSolder; not fitted
C22: 22µF; C_0805_2012Metric_Pad1.18x1.45mm_HandSolder; LCSC ID # C907991
D1: ESD8472MUT5G; D_0201_0603Metric; LCSC ID # C133346
D2: Power LED; LED_0603_1608Metric_Pad1.05x0.95mm_HandSolder; LCSC ID # C965804
FID1, FID2: Fiducial; Fiducial_1mm_Mask2mm
FL1, FL2: TA2003A; FL_Tai-Saw_TA2003A; not fitted
H1: TopLeft; MountingHole_2.7mm_M2.5_Pad_Via
H2: BottomLeft; MountingHole_2.7mm_M2.5_Pad_Via
H3: TopRight; MountingHole_2.7mm_M2.5_Pad_Via
H4: BottomRight; MountingHole_2.7mm_M2.5_Pad_Via
J1: Conn_Coaxial; U.FL_Hirose_U.FL-R-SMT-1_Vertical; LCSC ID # C88374
J2: PWR_IN; PinHeader_1x02_P2.54mm_Vertical_SMD_Pin1Right; LCSC ID # C41417359
L1, L2, L3: 68nH; L_Coilcraft_0402DC_1005Metric; LCSC ID # C3221883
R1, R3: 0Ω; R_0402_1005Metric_Pad0.72x0.64mm_HandSolder; not fitted
R2, R5, R6: 0Ω; R_0402_1005Metric_Pad0.72x0.64mm_HandSolder; LCSC ID # C4105840
R4: 52.3Ω; R_0402_1005Metric_Pad0.72x0.64mm_HandSolder; LCSC ID # C2076978
R7: 6.04kΩ; R_0402_1005Metric_Pad0.72x0.64mm_HandSolder; LCSC ID # C416563
R8: 1.96kΩΩ; R_0402_1005Metric_Pad0.72x0.64mm_HandSolder; LCSC ID # C2076939
R9, R10, R14, R16: 499Ω; R_0402_1005Metric_Pad0.72x0.64mm_HandSolder; LCSC ID # C2090004
R11, R12: 49.9Ω; R_0402_1005Metric_Pad0.72x0.64mm_HandSolder; LCSC ID # C490832
R13, R15: 10kΩ; R_0402_1005Metric_Pad0.72x0.64mm_HandSolder; LCSC ID # C191915
R17: 2.2kΩ; R_0402_1005Metric_Pad0.72x0.64mm_HandSolder; LCSC ID # C413087
RV1: 20kΩ; Potentiometer_Bourns_3214W_Vertical; LCSC ID # C780198
RV2: 200Ω; Potentiometer_Bourns_3214W_Vertical; LCSC ID # C780200
TP1: RF IN; TestPoint_Pad_D1.0mm
TP2: LNA1 IN; TestPoint_Pad_D1.0mm
TP3: LNA 1 OUT; TestPoint_Pad_D1.0mm
TP4: FL1 IN; TestPoint_Pad_D1.0mm
TP5: FL1 OUT; TestPoint_Pad_D1.0mm
TP6: LNA2 IN; TestPoint_Pad_D1.0mm
TP7: LNA2 OUT; TestPoint_Pad_D1.0mm
TP8: FL2 IN; TestPoint_Pad_D1.0mm
TP9: FL2 OUT; TestPoint_Pad_D1.0mm
TP10: PI ATTEN OUT; TestPoint_Pad_D1.0mm
TP11: LOGDET IN; TestPoint_Pad_D1.0mm
TP12: LOGDET CLPF; TestPoint_Keystone_5015_Micro_Mini; LCSC ID # C2906768
TP13: LOGDET VOUT; TestPoint_Keystone_5015_Micro_Mini; LCSC ID # C2906768
TP14: LOGDET VSET; TestPoint_Keystone_5015_Micro_Mini; LCSC ID # C2906768
TP15: LOGDET TADJ; TestPoint_Keystone_5015_Micro_Mini; LCSC ID # C2906768
TP16: BUF VOUT; TestPoint_Keystone_5015_Micro_Mini; LCSC ID # C2906768
TP17: DRV +IN; TestPoint_Keystone_5015_Micro_Mini; LCSC ID # C2906768
TP18: DRV -OUT; TestPoint_Keystone_5015_Micro_Mini; LCSC ID # C2906768
TP19: ADC AINN; TestPoint_Keystone_5015_Micro_Mini; LCSC ID # C2906768
TP20: ADC AINP; TestPoint_Keystone_5015_Micro_Mini; LCSC ID # C2906768
TP21: DRV VOCM; TestPoint_Keystone_5015_Micro_Mini; LCSC ID # C2906768
TP22: DRV -IN; TestPoint_Keystone_5015_Micro_Mini; LCSC ID # C2906768
TP23: DRV +OUT; TestPoint_Keystone_5015_Micro_Mini; LCSC ID # C2906768
U1, U2: TQP3M9036; U_Qorvo_TQP3M9036-QFN; LCSC ID # C920261
U3: ADL5513; LFCSP-16-1EP_3x3mm_P0.5mm_EP1.6x1.6mm; LCSC ID # C579160
U4: TLV3541IDBVR; SOT-23-5; LCSC ID # C845577
U5: AD8138; SOIC-8_3.9x4.9mm_P1.27mm; LCSC ID # C289695

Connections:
/3V3: C2.1, C3.1, C6.1, C7.1, C11.1, C14.1, C16.1, C17.1, C19.1, C20.1, C22.1, J2.1, L2.1, L3.1, R5.1, R6.1, R7.1, R13.2, R17.1, U4.5 (V+), U5.3 (V+)
/DRV_IN+: R9.2, R10.1, TP17.1 (1_1), U5.8 (+IN)
/DRV_IN-: R14.1, R16.1, TP22.1 (1_1), U5.1 (-IN)
/DRV_OUT+: R12.1, R14.2, TP23.1 (1_1), U5.4 (+OUT)
/DRV_OUT-: R10.2, R11.1, TP18.1 (1_1), U5.5 (-OUT)
GND: C2.2, C3.2, C6.2, C7.2, C9.1, C11.2, C12.2, C13.2, C14.2, C15.2, C16.2, C17.2, C18.1, C19.2, C20.2, C21.2, C22.2, D1.1 (A1), D2.1 (K), FL1.A (GND), FL1.C (GND), FL1.D (GND), FL1.F (GND), FL2.A (GND), FL2.C (GND), FL2.D (GND), FL2.F (GND), H1.1 (1_1), H2.1 (1_1), H3.1 (1_1), H4.1 (1_1), J1.2 (Ext), J2.2, L1.2, R1.1, R3.1, R4.2, R8.2, R15.2, R16.2, RV1.3, U1.1 (NC), U1.3 (NC), U1.4 (NC), U1.5 (NC), U1.6 (Shutdown), U1.8 (NC), U1.EP (GND), U2.1 (NC), U2.3 (NC), U2.4 (NC), U2.5 (NC), U2.6 (Shutdown), U2.8 (NC), U2.EP (GND), U3.5 (NC), U3.6 (NC), U3.7 (NC), U3.8 (NC), U3.10 (COMM), U3.13 (NC), U3.15 (NC), U3.16 (NC), U3.17 (COMM), U4.2 (V-), U5.6 (V-)
unnamed: C10.1, R2.2, R3.2, R4.1, TP10.1 (1_1)
unnamed: C12.1, R5.2, U3.1 (VPOS)
unnamed: C13.1, R6.2, U3.4 (VPOS)
unnamed: C18.2, R11.2, TP19.1 (1_1)
unnamed: C21.1, R12.2, TP20.1 (1_1)
unnamed: C1.2, D1.2 (A2), J1.1 (In), L1.1, TP1.1 (1_1)
unnamed: D2.2 (A), R17.2
unnamed: C4.2, FL1.B (IN), TP4.1 (1_1)
unnamed: C5.2, FL1.E (OUT), TP5.1 (1_1)
unnamed: C8.2, FL2.B (IN), TP8.1 (1_1)
unnamed: FL2.E (OUT), R1.2, R2.1, TP9.1 (1_1)
unnamed: R7.2, RV2.1
unnamed: R8.1, RV2.3
unnamed: C1.1, TP2.1 (1_1), U1.2 (RF_In)
unnamed: C4.1, L2.2, TP3.1 (1_1), U1.7 (RF_Out)
unnamed: C5.1, TP6.1 (1_1), U2.2 (RF_In)
unnamed: C8.1, L3.2, TP7.1 (1_1), U2.7 (RF_Out)
unnamed: C15.1, TP12.1 (1_1), U3.14 (CLPF)
unnamed: C10.2, TP11.1 (1_1), U3.2 (INHI)
unnamed: C9.2, U3.3 (INLO)
unnamed: RV2.2, TP15.1 (1_1), U3.9 (TADJ)
unnamed: RV1.1, TP13.1 (1_1), U3.12 (VOUT), U4.3 (+)
unnamed: RV1.2, TP14.1 (1_1), U3.11 (VSET)
unnamed: R9.1, TP16.1 (1_1), U4.1, U4.4 (-)
unnamed: R13.1, R15.1, TP21.1 (1_1), U5.2 (VOCM)
